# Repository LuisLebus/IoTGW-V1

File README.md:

<div id="top">

</div>

<!-- LOGO AND TITTLE -->
<div align="center">
  <h3 align="center">Luis Lebus</h3>

  [![LinkedIn][linkedin-shield]][linkedin-url]
  [![Portfolio][portfolio-shield]][portfolio-url]
  
  <br>
  
  <h3 align="center">IoTGW-V1</h3>
  <p align="center">Gateway IoT V1</p>
</div>

<!-- TABLE OF CONTENTS -->
<details>
  <summary>Table of Contents</summary>
  <ol>
    <li>
      <a href="#description">Description</a>
      <ul>
        <li><a href="#built-with">Built With</a></li>
      </ul>
    </li>
    <li><a href="#image">Image</a></li>
    <li><a href="#contact">Contact</a></li>
    <li><a href="#acknowledgments">Acknowledgments</a></li>
  </ol>
</details>

<!-- ABOUT THE PROJECT -->
## Description

This project is an IoT gateway. 
<br>
This board has CAN, Modbus RTU, WiFi and Ethernet communication.

<p align="right">(<a href="#top">back to top</a>)</p>

### Built With

* [KiCad v5.1.12](https://www.kicad.org/)

<p align="right">(<a href="#top">back to top</a>)</p>

<!-- ABOUT THE PROJECT -->
## Image

<p align="right">(<a href="#top">back to top</a>)</p>

<!-- CONTACT -->
## Contact

Luis Lebus - luislebus@gmail.com

* [LinkedIn](https://www.linkedin.com/in/LuisLebus)
* [Portfolio](https://luislebus.github.io/portfolio)

<p align="right">(<a href="#top">back to top</a>)</p>

<!-- ACKNOWLEDGMENTS -->
## Acknowledgments

<p align="right">(<a href="#top">back to top</a>)</p>

<!-- MARKDOWN LINKS & IMAGES -->
[linkedin-shield]: https://img.shields.io/badge/LinkedIn-0077B5?style=for-the-badge&logo=linkedin&logoColor=white
[linkedin-url]: https://www.linkedin.com/in/LuisLebus
[portfolio-shield]: https://img.shields.io/badge/PORTFOLIO%20-%23323330.svg?&style=for-the-badge&logo=badges&logoColor=black&color=0000FF
[portfolio-url]: https://luislebus.github.io/portfolio

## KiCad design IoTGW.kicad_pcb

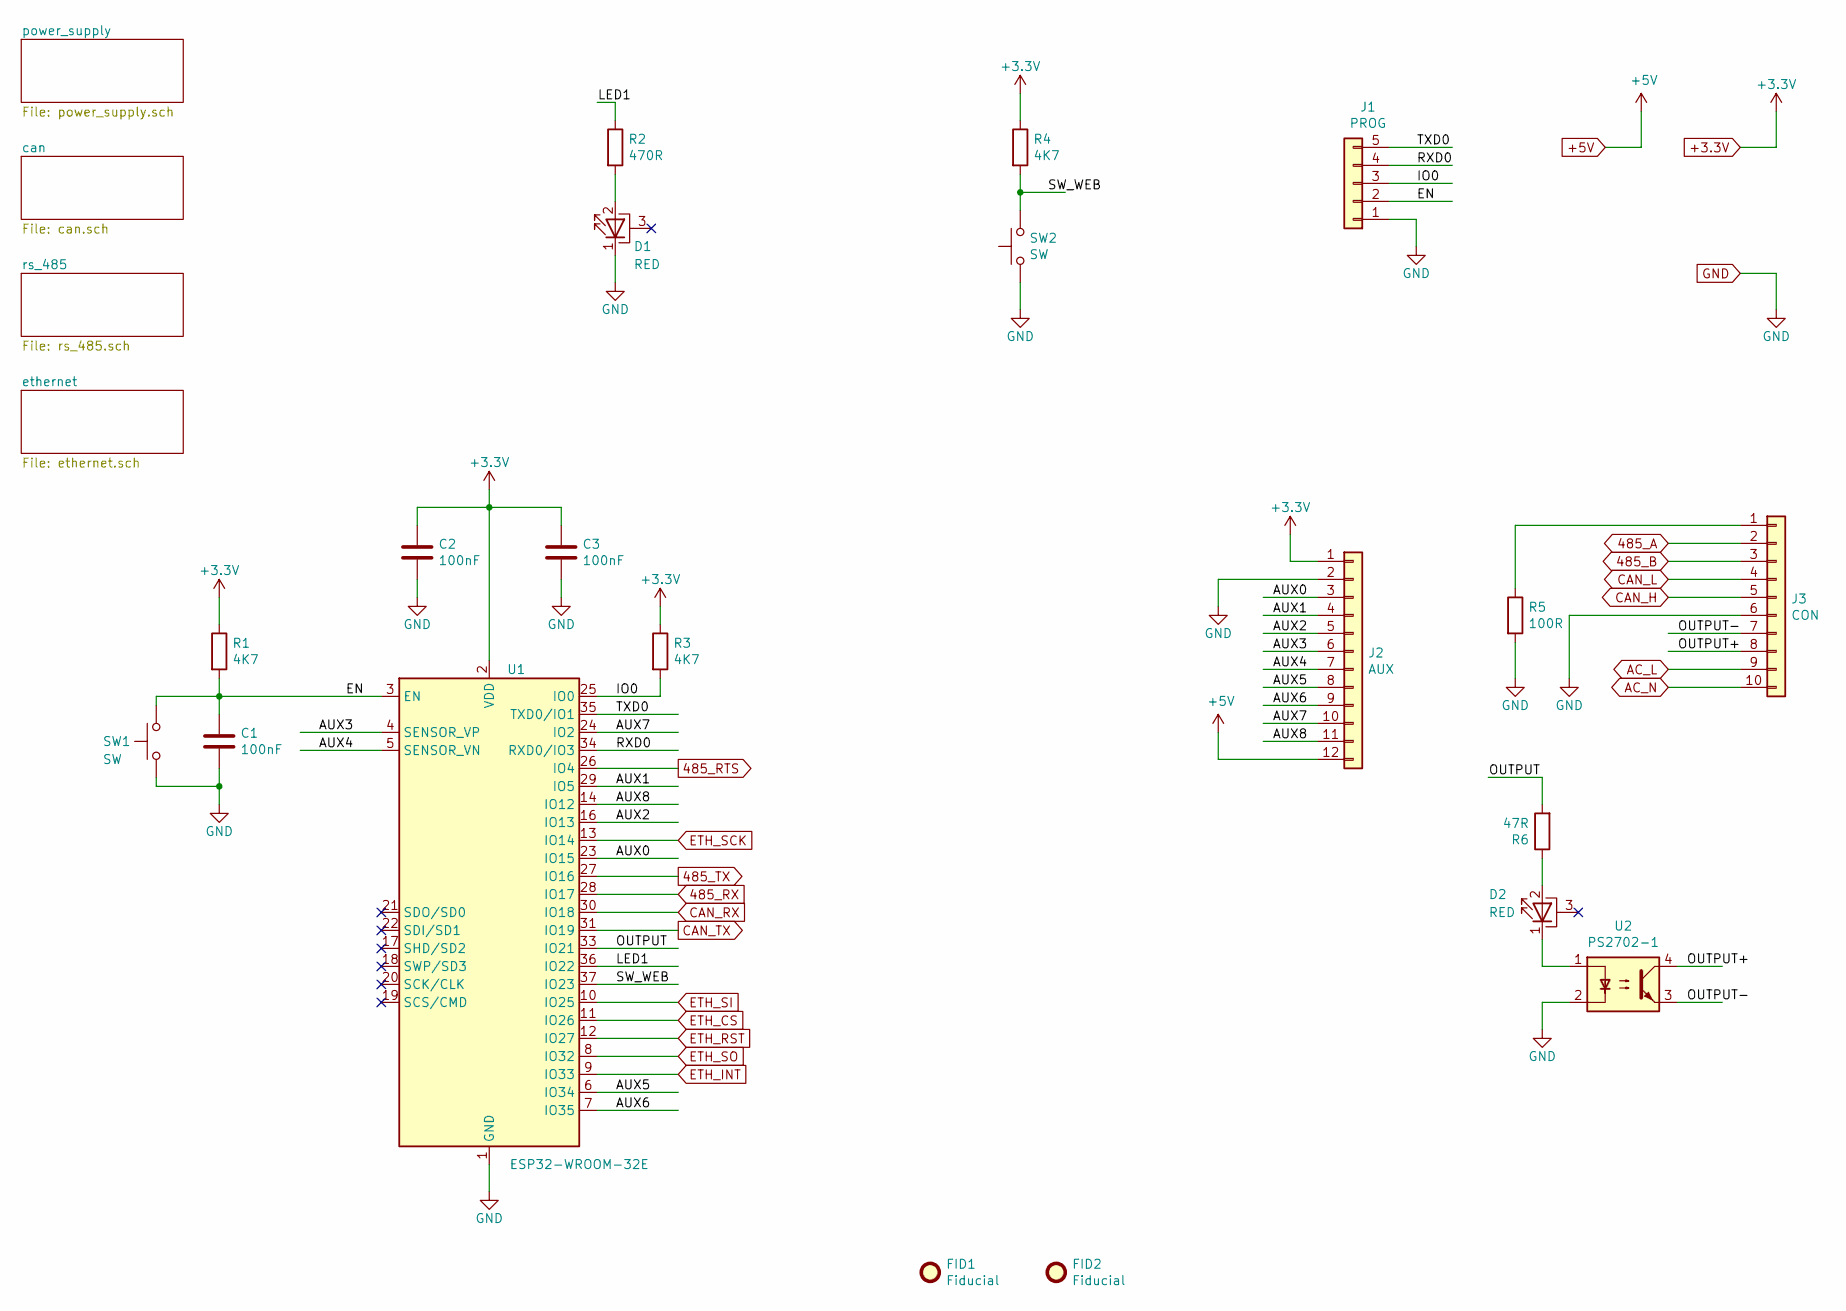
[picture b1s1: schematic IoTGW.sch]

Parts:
C1, C2, C3: 100nF; C_0805_2012Metric
D1, D2: RED; LTST-S321KRKT
FID1, FID2: Fiducial; Fiducial_1.5mm_Mask3mm
J1: PROG; PinSocket_1x05_P2.54mm_Vertical
J2: AUX; PinSocket_1x12_P2.54mm_Vertical
J3: CON; 1759091
R1, R3, R4: 4K7; R_0805_2012Metric
R2: 470R; R_0805_2012Metric
R5: 100R; R_1206_3216Metric
R6: 47R; R_0805_2012Metric
SW1, SW2: SW; SW_Tactile_SPST_Angled_PTS645Vx83-2LFS
U1: ESP32-WROOM-32E; ESP32-WROOM-32
U2: PS2702-1; PS2702-1-F3-K-A

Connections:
485_A: J3.2; also elsewhere on the board
485_B: J3.3; also elsewhere on the board
485_RTS: U1.26 (IO4); also elsewhere on the board
485_RX: U1.28 (IO17); also elsewhere on the board
485_TX: U1.27 (IO16); also elsewhere on the board
+3.3V: C2.1, C3.1, J2.1, R1.1, R3.1, R4.1, U1.2 (VDD); also elsewhere on the board
+5V: J2.12; also elsewhere on the board
/AUX0: J2.3, U1.23 (IO15)
/AUX1: J2.4, U1.29 (IO5)
/AUX2: J2.5, U1.16 (IO13)
/AUX3: J2.6, U1.4 (SENSOR_VP)
/AUX4: J2.7, U1.5 (SENSOR_VN)
/AUX5: J2.8, U1.6 (IO34)
/AUX6: J2.9, U1.7 (IO35)
/AUX7: J2.10, U1.24 (IO2)
/AUX8: J2.11, U1.14 (IO12)
/EN: C1.1, J1.2, R1.2, SW1.2, U1.3 (EN)
/IO0: J1.3, R3.2, U1.25 (IO0)
/LED1: R2.1, U1.36 (IO22)
/OUTPUT: R6.2, U1.33 (IO21)
/OUTPUT+: J3.8, U2.4
/OUTPUT-: J3.7, U2.3
/RXD0: J1.4, U1.34 (RXD0/IO3)
/SW_WEB: R4.2, SW2.2, U1.37 (IO23)
/TXD0: J1.5, U1.35 (TXD0/IO1)
AC_L: J3.9; also elsewhere on the board
AC_N: J3.10; also elsewhere on the board
CAN_H: J3.5; also elsewhere on the board
CAN_L: J3.4; also elsewhere on the board
CAN_RX: U1.30 (IO18); also elsewhere on the board
CAN_TX: U1.31 (IO19); also elsewhere on the board
ETH_CS: U1.11 (IO26); also elsewhere on the board
ETH_INT: U1.9 (IO33); also elsewhere on the board
ETH_RST: U1.12 (IO27); also elsewhere on the board
ETH_SCK: U1.13 (IO14); also elsewhere on the board
ETH_SI: U1.10 (IO25); also elsewhere on the board
ETH_SO: U1.8 (IO32); also elsewhere on the board
GND: C1.2, C2.2, C3.2, D1.1 (K), J1.1, J2.2, J3.6, R5.2, SW1.1, SW2.1, U1.1 (GND), U1.15 (GND), U1.38 (GND), U1.39 (GND), U2.2; also elsewhere on the board
unnamed: D1.2 (A), R2.2
unnamed: D2.1 (K), U2.1
unnamed: D2.2 (A), R6.1
unnamed: J3.1, R5.1

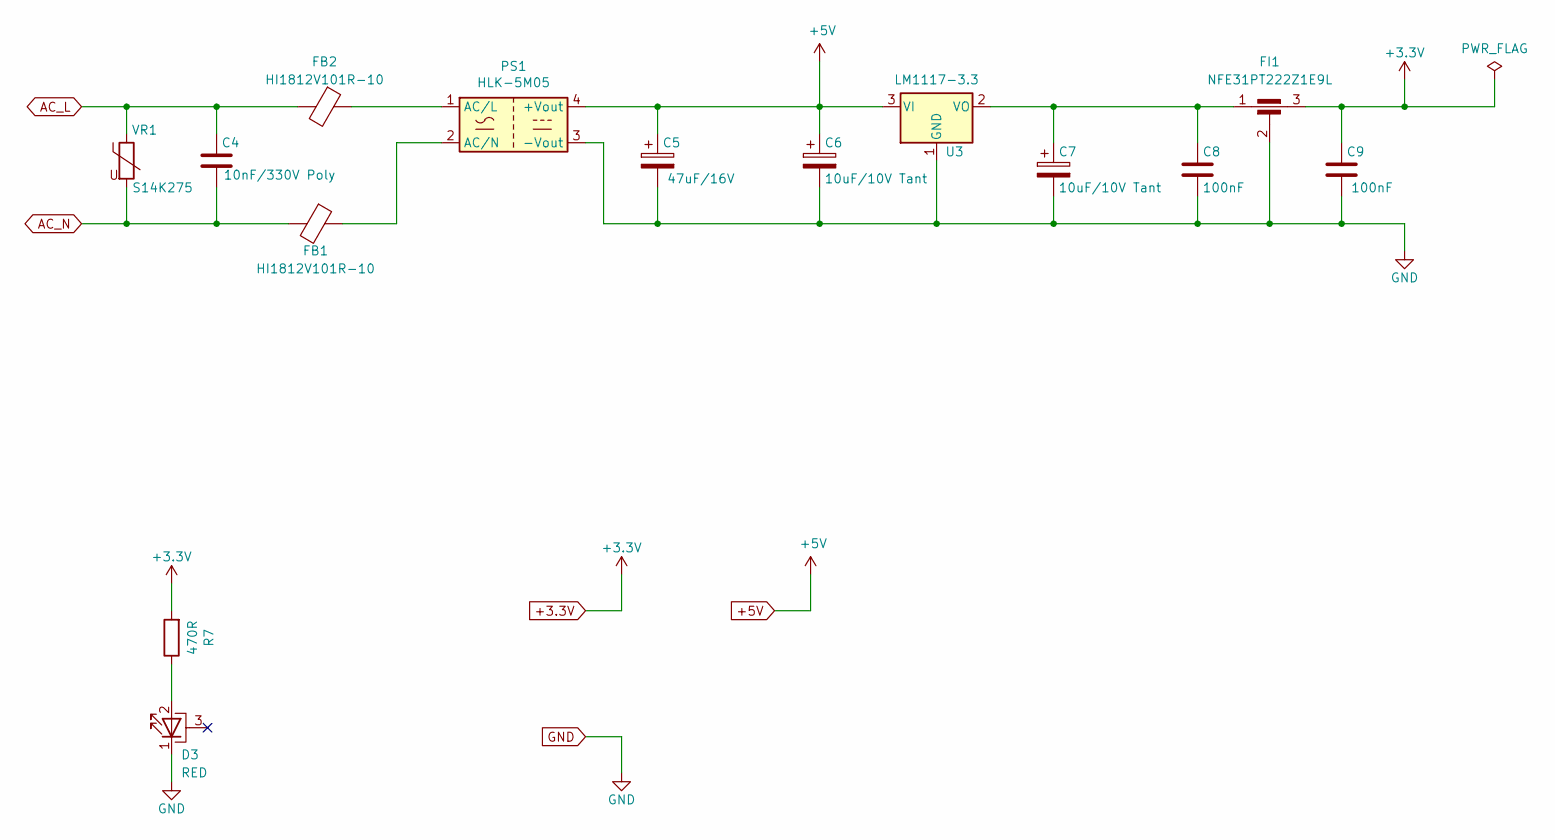
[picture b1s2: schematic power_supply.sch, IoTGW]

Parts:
C4: 10nF/330V Poly; C_Rect_L13.0mm_W4.0mm_P10.00mm_FKS3_FKP3_MKS4
C5: 47uF/16V; CP_Elec_5x5.4
C6, C7: 10uF/10V Tant; CP_EIA-3216-18_Kemet-A
C8, C9: 100nF; C_0805_2012Metric
D3: RED; LTST-S321KRKT
FB1, FB2: HI1812V101R-10; L_1812_4532Metric
FI1: NFE31PT222Z1E9L
PS1: HLK-5M05
R7: 470R; R_0805_2012Metric
U3: LM1117-3.3; SOT-223-3_TabPin2
VR1: S14K275; RV_Disc_D15.5mm_W5mm_P7.5mm

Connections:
+3.3V: C9.1, FI1.3, R7.2; also elsewhere on the board
+5V: C5.1, C6.1, PS1.4 (+Vout), U3.3 (VI); also elsewhere on the board
AC_L: C4.1, FB2.2, VR1.1; also elsewhere on the board
AC_N: C4.2, FB1.2, VR1.2; also elsewhere on the board
GND: C5.2, C6.2, C7.2, C8.2, C9.2, D3.1 (K), FI1.2, PS1.3 (-Vout), U3.1 (GND); also elsewhere on the board
unnamed: C7.1, C8.1, FI1.1, U3.2 (VO)
unnamed: D3.2 (A), R7.1
unnamed: FB1.1, PS1.2 (AC/N)
unnamed: FB2.1, PS1.1 (AC/L)

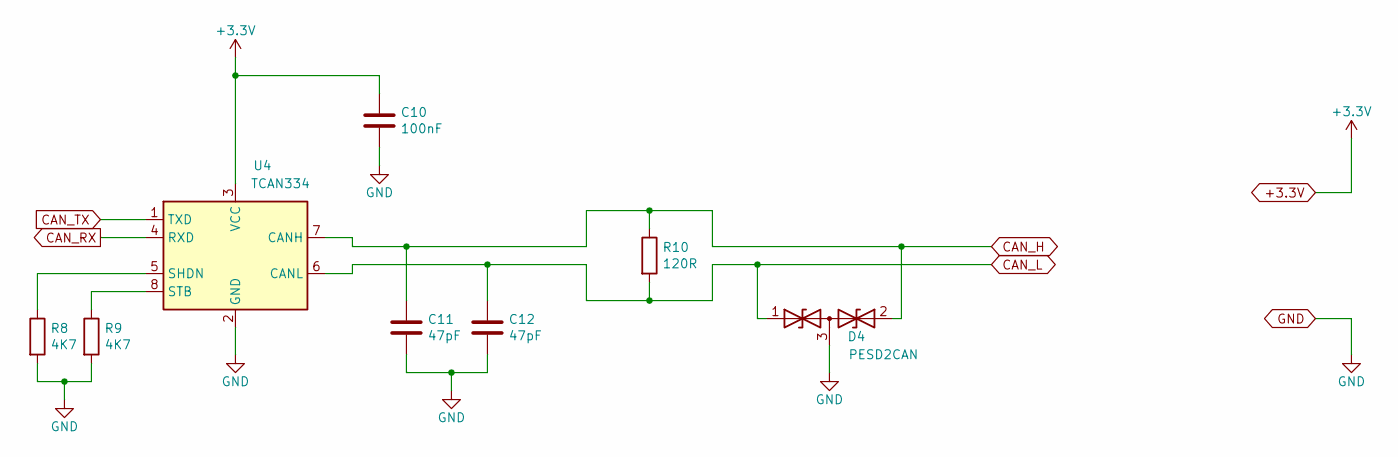
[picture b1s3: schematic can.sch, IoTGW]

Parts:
C10: 100nF; C_0805_2012Metric
C11, C12: 47pF; C_0805_2012Metric
D4: PESD2CAN; SOT-23
R8, R9: 4K7; R_0805_2012Metric
R10: 120R; R_1206_3216Metric
U4: TCAN334; SOIC-8_3.9x4.9mm_P1.27mm

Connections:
+3.3V: C10.1, U4.3 (VCC); also elsewhere on the board
CAN_H: C11.1, D4.2 (A2), R10.1, U4.7 (CANH); also elsewhere on the board
CAN_L: C12.1, D4.1 (A1), R10.2, U4.6 (CANL); also elsewhere on the board
CAN_RX: U4.4 (RXD); also elsewhere on the board
CAN_TX: U4.1 (TXD); also elsewhere on the board
GND: C10.2, C11.2, C12.2, D4.3 (common), R8.2, R9.2, U4.2 (GND); also elsewhere on the board
unnamed: R8.1, U4.5 (SHDN)
unnamed: R9.1, U4.8 (STB)

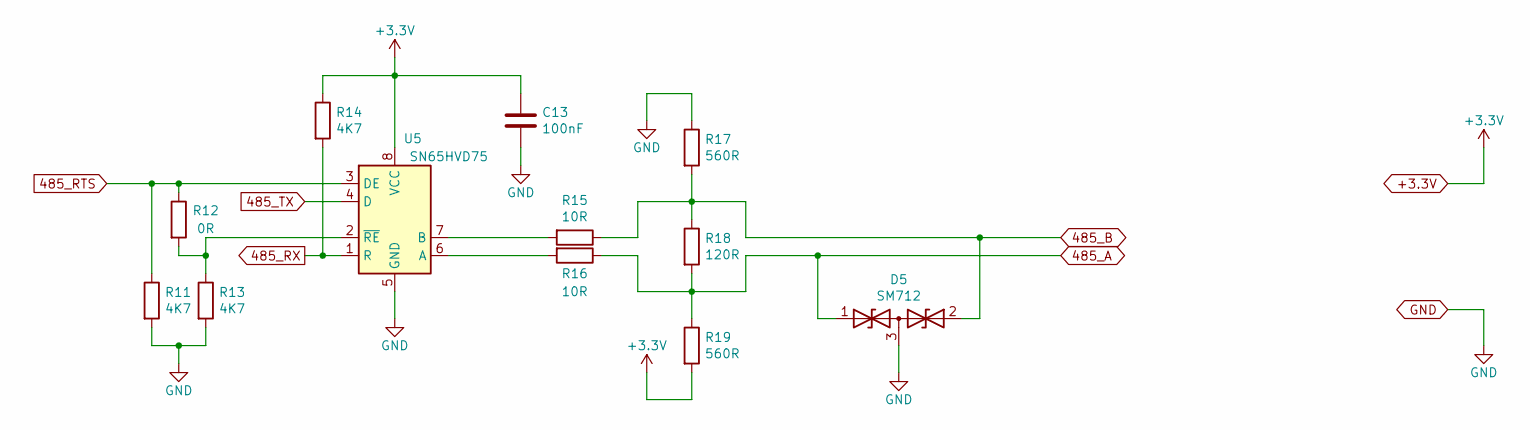
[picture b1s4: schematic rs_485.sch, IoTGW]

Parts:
C13: 100nF; C_0805_2012Metric
D5: SM712; SOT-23
R11, R13, R14: 4K7; R_0805_2012Metric
R12: 0R; R_0805_2012Metric
R15, R16: 10R; R_0805_2012Metric
R17, R19: 560R; R_0805_2012Metric
R18: 120R; R_1206_3216Metric
U5: SN65HVD75; SOIC-8_3.9x4.9mm_P1.27mm

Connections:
485_A: D5.1 (A1), R16.1, R18.2, R19.1; also elsewhere on the board
485_B: D5.2 (A2), R15.1, R17.2, R18.1; also elsewhere on the board
485_RTS: R11.1, R12.1, U5.3 (DE); also elsewhere on the board
485_RX: R14.2, U5.1 (R); also elsewhere on the board
485_TX: U5.4 (D); also elsewhere on the board
+3.3V: C13.1, R14.1, R19.2, U5.8 (VCC); also elsewhere on the board
GND: C13.2, D5.3 (common), R11.2, R13.2, R17.1, U5.5 (GND); also elsewhere on the board
unnamed: R12.2, R13.1, U5.2 (~RE)
unnamed: R15.2, U5.7 (B)
unnamed: R16.2, U5.6 (A)

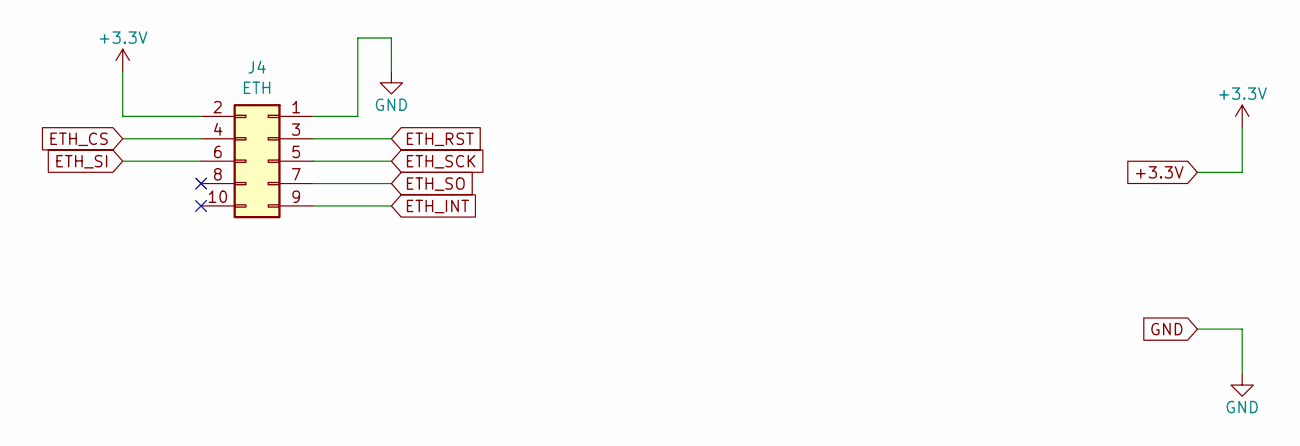
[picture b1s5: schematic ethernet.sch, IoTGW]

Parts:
J4: ETH; PinSocket_2x05_P2.54mm_Vertical

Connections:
+3.3V: J4.2; also elsewhere on the board
ETH_CS: J4.4; also elsewhere on the board
ETH_INT: J4.9; also elsewhere on the board
ETH_RST: J4.3; also elsewhere on the board
ETH_SCK: J4.5; also elsewhere on the board
ETH_SI: J4.6; also elsewhere on the board
ETH_SO: J4.7; also elsewhere on the board
GND: J4.1; also elsewhere on the board

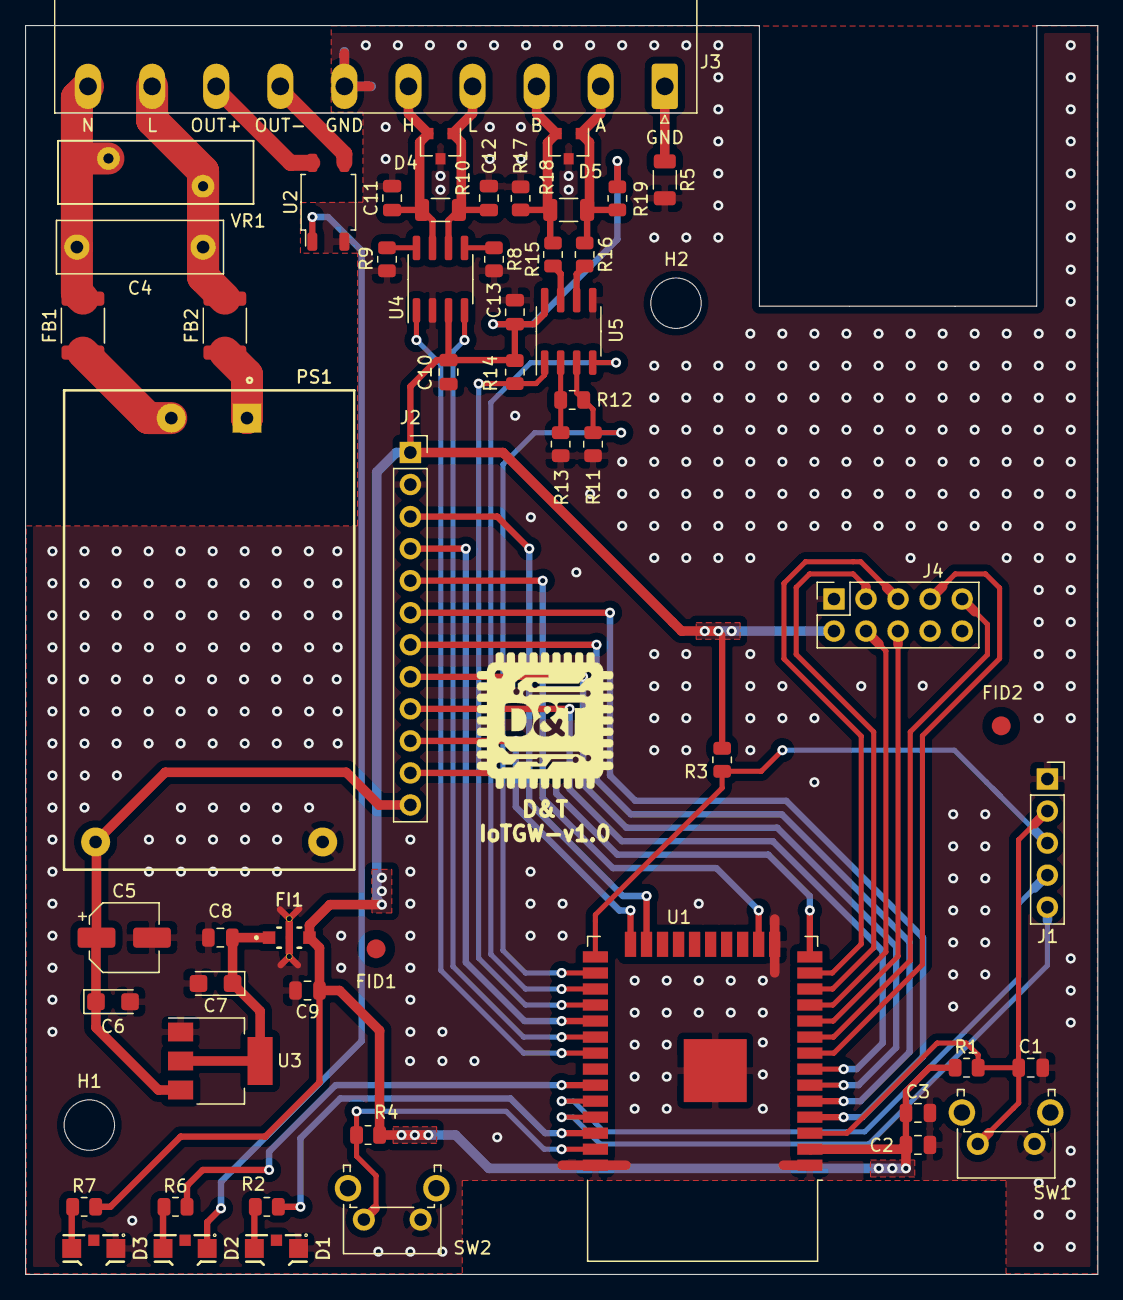
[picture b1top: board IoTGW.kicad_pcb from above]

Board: 2 copper layers, 85.0 x 99.0 mm, 57 parts (0 on the bottom side), 51 nets.

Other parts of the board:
H1, H2: MountingHole_4mm
